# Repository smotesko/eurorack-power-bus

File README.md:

Small Eurorack power distribution board. See [blog posts tagged "power-kit"](https://smotesko.com/tags#power-kit) for details.

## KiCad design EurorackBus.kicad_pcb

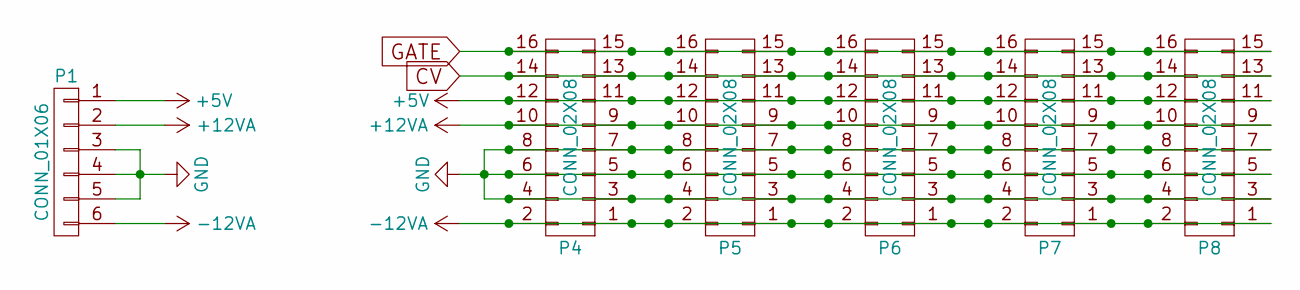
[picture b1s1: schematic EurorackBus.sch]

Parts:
P1: CONN_01X06
P4, P5, P6, P7, P8: CONN_02X08; Molex_C-Grid_2x8_noPeg

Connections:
+5V: P1.1, P4.11, P4.12, P5.11, P5.12, P6.11, P6.12, P7.11, P7.12, P8.11, P8.12
+12VA: P1.2, P4.9, P4.10, P5.9, P5.10, P6.9, P6.10, P7.9, P7.10, P8.9, P8.10
-12VA: P1.6, P4.1, P4.2, P5.1, P5.2, P6.1, P6.2, P7.1, P7.2, P8.1, P8.2
CV: P4.13, P4.14, P5.13, P5.14, P6.13, P6.14, P7.13, P7.14, P8.13, P8.14
GATE: P4.15, P4.16, P5.15, P5.16, P6.15, P6.16, P7.15, P7.16, P8.15, P8.16
GND: P1.3, P1.4, P1.5, P4.3, P4.4, P4.5, P4.6, P4.7, P4.8, P5.3, P5.4, P5.5, P5.6, P5.7, P5.8, P6.3, P6.4, P6.5, P6.6, P6.7, P6.8, P7.3, P7.4, P7.5, P7.6, P7.7, P7.8, P8.3, P8.4, P8.5, P8.6, P8.7, P8.8

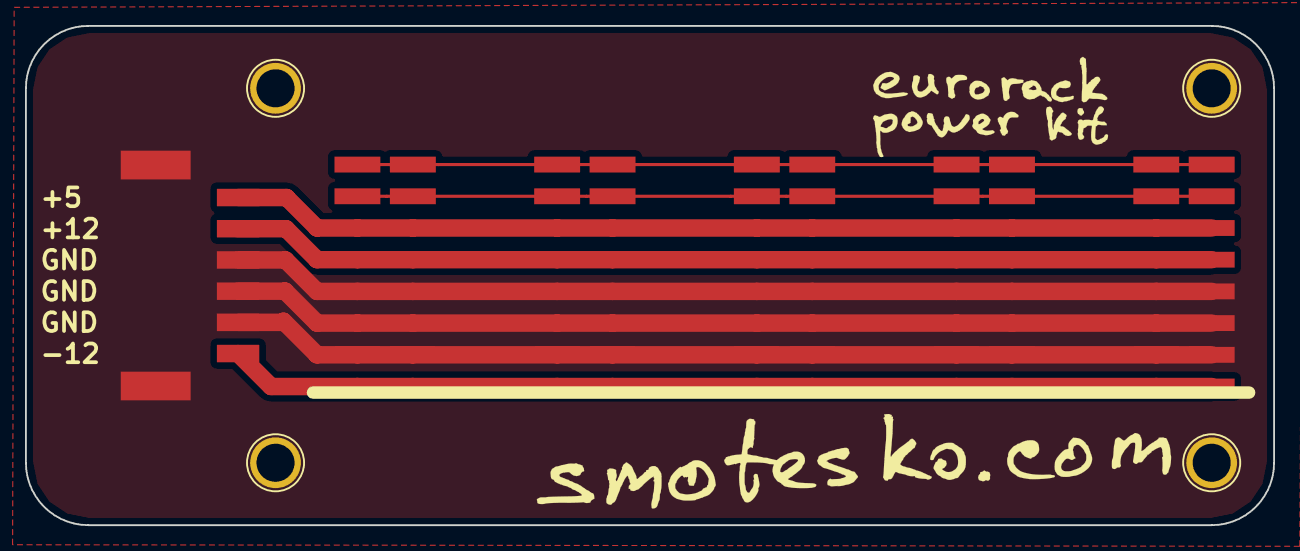
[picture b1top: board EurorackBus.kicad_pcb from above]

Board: 2 copper layers, 100.0 x 40.0 mm, 6 parts (0 on the bottom side), 6 nets.

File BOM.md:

| Component          | Description                                | Part number      |
|--------------------|--------------------------------------------|------------------|
| P1                 | PCB terminal block, SMD                    | Phoenix 1814676  |
| P4, P5, P6, P7, P8 | 2.54mm Pitch C-Grid® Header, Surface Mount | Molex 15-91-0160 |

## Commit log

2017-09-02 add BOM
